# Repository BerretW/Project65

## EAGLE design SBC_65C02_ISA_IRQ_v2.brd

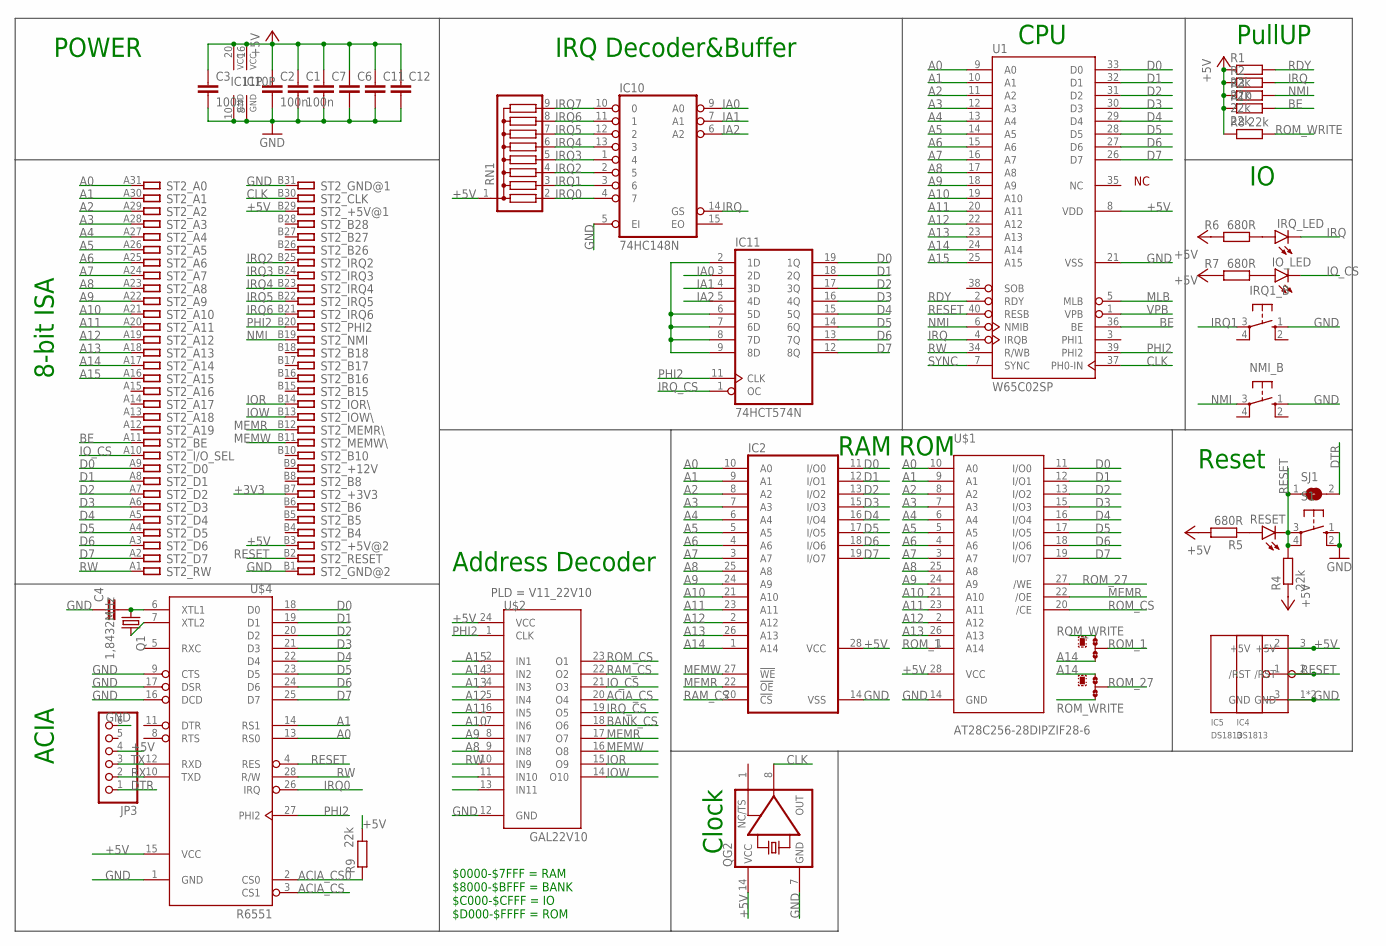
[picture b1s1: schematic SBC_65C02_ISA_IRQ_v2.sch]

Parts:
C1, C2, C3: 100n; C050-025X075
C4: C-EU025-030X050; C025-030X050
C6, C7, C11, C12: C-EU050-035X075; C050-035X075
IC2: 62256P; DIL28-6
IC4: DS1813; SOT223
IC5: DS1813; TO-92
IC10: 74HC148N; DIL16
IC11: 74HCT574N; DIL20
IO_LED: LED5MM
IRQ1_B: 10-XX; B3F-10XX
IRQ_LED: LED5MM
JP3: PINHD-1X6/90; 1X06/90
NMI_B: 10-XX; B3F-10XX
Q1: 1,8432MHz; HC49/S
QG2: XO-14; DIL14S
R1, R2, R3, R4, R8, R9, R10: 22k; 0207/10
R5, R6, R7: 680R; 0207/10
RESET: LED5MM
RN1: G08R; SIL9
ROM_1, ROM_27: 0R-JUMPA; A0R-JMP
S1: 10-XX; B3F-10XX
SJ1: SJ
ST2: IBM8BIT_ISA; IBM8BIT
U1: W65C02SP; DIP-40
U$1: AT28C256-28DIPZIF28-6; 228-1277-00-0602J
U$2: GAL22V10; DIL28_1
U$4: R6551; DIP-28

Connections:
+3V3: ST2.B7
+5V: C1.1, C2.1, C3.1, C6.1, C7.1, C11.1, C12.1, IC2.28 (VCC), IC4.3 (+5V), IC5.2 (+5V), IC10.16 (VCC), IC11.20 (VCC), JP3.4, QG2.14 (VCC), R1.1, R2.1, R3.1, R4.1, R5.2, R6.2, R7.2, R8.1, R9.2, R10.1, RN1.1, ST2.B3, ST2.B29, U1.8 (VDD), U$1.28 (VCC), U$2.24 (VCC), U$4.15 (VCC)
A0: IC2.10 (A0), ST2.A31, U1.9 (A0), U$1.10 (A0), U$4.13 (RS0)
A1: IC2.9 (A1), ST2.A30, U1.10 (A1), U$1.9 (A1), U$4.14 (RS1)
A2: IC2.8 (A2), ST2.A29, U1.11 (A2), U$1.8 (A2)
A3: IC2.7 (A3), ST2.A28, U1.12 (A3), U$1.7 (A3)
A4: IC2.6 (A4), ST2.A27, U1.13 (A4), U$1.6 (A4)
A5: IC2.5 (A5), ST2.A26, U1.14 (A5), U$1.5 (A5)
A6: IC2.4 (A6), ST2.A25, U1.15 (A6), U$1.4 (A6)
A7: IC2.3 (A7), ST2.A24, U1.16 (A7), U$1.3 (A7)
A8: IC2.25 (A8), ST2.A23, U1.17 (A8), U$1.25 (A8), U$2.9 (IN8)
A9: IC2.24 (A9), ST2.A22, U1.18 (A9), U$1.24 (A9), U$2.8 (IN7)
A10: IC2.21 (A10), ST2.A21, U1.19 (A10), U$1.21 (A10), U$2.7 (IN6)
A11: IC2.23 (A11), ST2.A20, U1.20 (A11), U$1.23 (A11), U$2.6 (IN5)
A12: IC2.2 (A12), ST2.A19, U1.22 (A12), U$1.2 (A12), U$2.5 (IN4)
A13: IC2.26 (A13), ST2.A18, U1.23 (A13), U$1.26 (A13), U$2.4 (IN3)
A14: IC2.1 (A14), ROM_1.3, ROM_27.1, ST2.A17, U1.24 (A14), U$2.3 (IN2)
A15: ST2.A16, U1.25 (A15), U$2.2 (IN1)
ACIA_CS: U$2.20 (O4), U$4.3 (CS1)
ACIA_CS0: R9.1, U$4.2 (CS0)
BANK_CS: U$2.18 (O6)
BE: R10.2, ST2.A11, U1.36 (BE)
CLK: QG2.8 (OUT), ST2.B30, U1.37 (PH0-IN)
D0: IC2.11 (I/O0), IC11.19 (1Q), ST2.A9, U1.33 (D0), U$1.11 (I/O0), U$4.18 (D0)
D1: IC2.12 (I/O1), IC11.18 (2Q), ST2.A8, U1.32 (D1), U$1.12 (I/O1), U$4.19 (D1)
D2: IC2.13 (I/O2), IC11.17 (3Q), ST2.A7, U1.31 (D2), U$1.13 (I/O2), U$4.20 (D2)
D3: IC2.15 (I/O3), IC11.16 (4Q), ST2.A6, U1.30 (D3), U$1.15 (I/O3), U$4.21 (D3)
D4: IC2.16 (I/O4), IC11.15 (5Q), ST2.A5, U1.29 (D4), U$1.16 (I/O4), U$4.22 (D4)
D5: IC2.17 (I/O5), IC11.14 (6Q), ST2.A4, U1.28 (D5), U$1.17 (I/O5), U$4.23 (D5)
D6: IC2.18 (I/O6), IC11.13 (7Q), ST2.A3, U1.27 (D6), U$1.18 (I/O6), U$4.24 (D6)
D7: IC2.19 (I/O7), IC11.12 (8Q), ST2.A2, U1.26 (D7), U$1.19 (I/O7), U$4.25 (D7)
DTR: JP3.1, SJ1.2
GND: C1.2, C2.2, C3.2, C4.1, C6.2, C7.2, C11.2, C12.2, IC2.14 (VSS), IC4.1 (GND), IC4.4 (GND), IC5.3 (GND), IC10.5 (EI), IC10.8 (GND), IC11.10 (GND), IRQ1_B.1 (S), JP3.6, NMI_B.1 (S), QG2.7 (GND), S1.1 (S), S1.2 (S1), ST2.B1, ST2.B31, U1.21 (VSS), U$1.14 (GND), U$2.12 (GND), U$4.1 (GND), U$4.9 (CTS), U$4.16 (DCD), U$4.17 (DSR)
IA0: IC10.9 (A0), IC11.3 (2D)
IA1: IC10.7 (A1), IC11.4 (3D)
IA2: IC10.6 (A2), IC11.5 (4D)
IOR: ST2.B14, U$2.15 (O9)
IOW: ST2.B13, U$2.14 (O10)
IO_CS: IO_LED.K (C), ST2.A10, U$2.21 (O3)
IRQ: IC10.14 (GS), IRQ_LED.K (C), R2.2, U1.4 (IRQB)
IRQ0: IC10.4 (7), RN1.2, U$4.26 (IRQ)
IRQ1: IC10.3 (6), IRQ1_B.3, RN1.3
IRQ2: IC10.2 (5), RN1.4, ST2.B25
IRQ3: IC10.1 (4), RN1.5, ST2.B24
IRQ4: IC10.13 (3), RN1.6, ST2.B23
IRQ5: IC10.12 (2), RN1.7, ST2.B22
IRQ6: IC10.11 (1), RN1.8, ST2.B21
IRQ7: IC10.10 (0), RN1.9
IRQ_CS: IC11.1 (OC), U$2.19 (O5)
MEMR: IC2.22 (!OE), ST2.B12, U$1.22 (/OE), U$2.17 (O7)
MEMW: IC2.27 (!WE), ST2.B11, U$2.16 (O8)
MLB: U1.5 (MLB)
unnamed: IRQ_LED.A, R6.1
unnamed: R5.1, RESET.A
unnamed: IO_LED.A, R7.1
unnamed: IC11.2 (1D), IC11.6 (5D), IC11.7 (6D), IC11.8 (7D), IC11.9 (8D)
unnamed: C4.2, Q1.1, U$4.6 (XTL1)
unnamed: Q1.2, U$4.7 (XTL2)
NMI: NMI_B.3, R3.2, ST2.B19, U1.6 (NMIB)
PHI2: IC11.11 (CLK), ST2.B20, U1.39 (PHI2), U$2.1 (CLK), U$4.27 (PHI2)
RAM_CS: IC2.20 (!CS), U$2.22 (O2)
RDY: R1.2, U1.2 (RDY)
RESET: IC4.2 (/RST), IC5.1 (/RST), R4.2, RESET.K (C), S1.3, S1.4 (P1), SJ1.1, ST2.B2, U1.40 (RESB), U$4.4 (RES)
ROM_1: ROM_1.2, U$1.1 (A14)
ROM_27: ROM_27.2, U$1.27 (/WE)
ROM_CS: U$1.20 (/CE), U$2.23 (O1)
ROM_WRITE: R8.2, ROM_1.1, ROM_27.3
RW: ST2.A1, U1.34 (R/WB), U$2.10 (IN9), U$4.28 (R/W)
RX: JP3.2, U$4.10 (TXD)
SYNC: U1.7 (SYNC)
TX: JP3.3, U$4.12 (RXD)
VPB: U1.1 (VPB)

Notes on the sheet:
$0000-$7FFF = RAM $8000-$BFFF = BANK $C000-$CFFF = IO $D000-$FFFF = ROM
ACIA
Address Decoder
Reset
CPU
POWER
8-bit ISA
RAM ROM
Clock
PullUP
PLD = V11_22V10
IRQ Decoder&Buffer

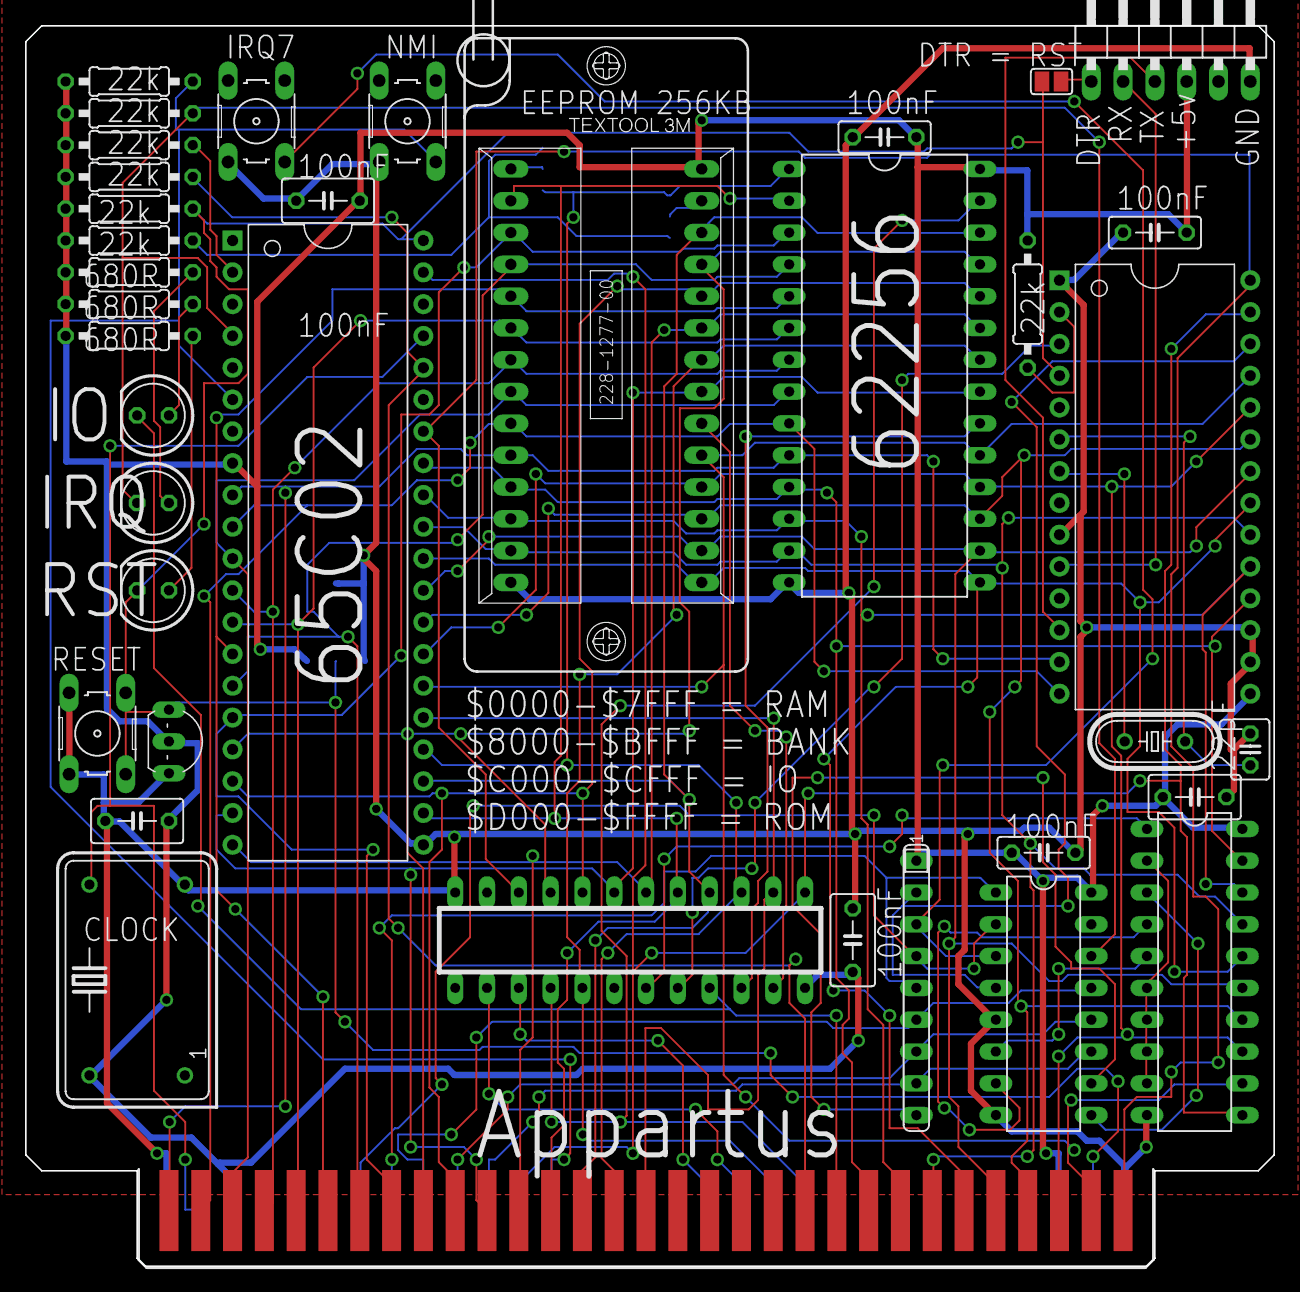
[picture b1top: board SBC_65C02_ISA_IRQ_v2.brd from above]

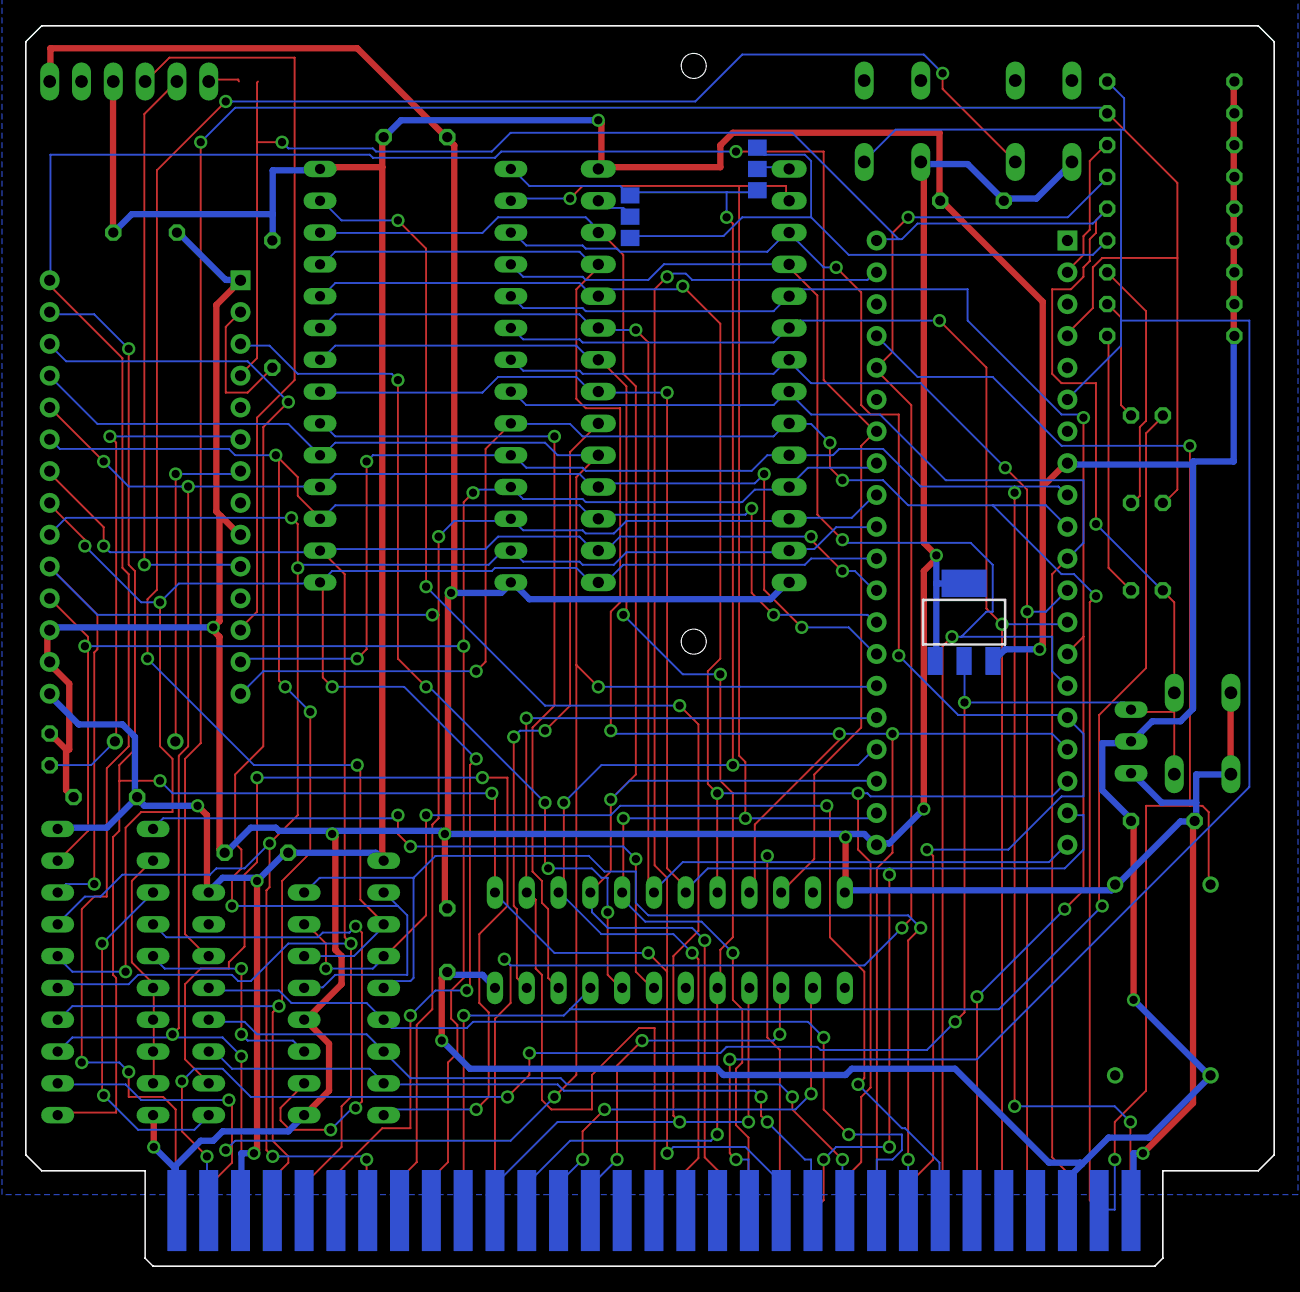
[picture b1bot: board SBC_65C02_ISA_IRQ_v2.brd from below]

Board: 2 copper layers, 99.7 x 99.1 mm, 41 parts (3 on the bottom side), 67 nets.

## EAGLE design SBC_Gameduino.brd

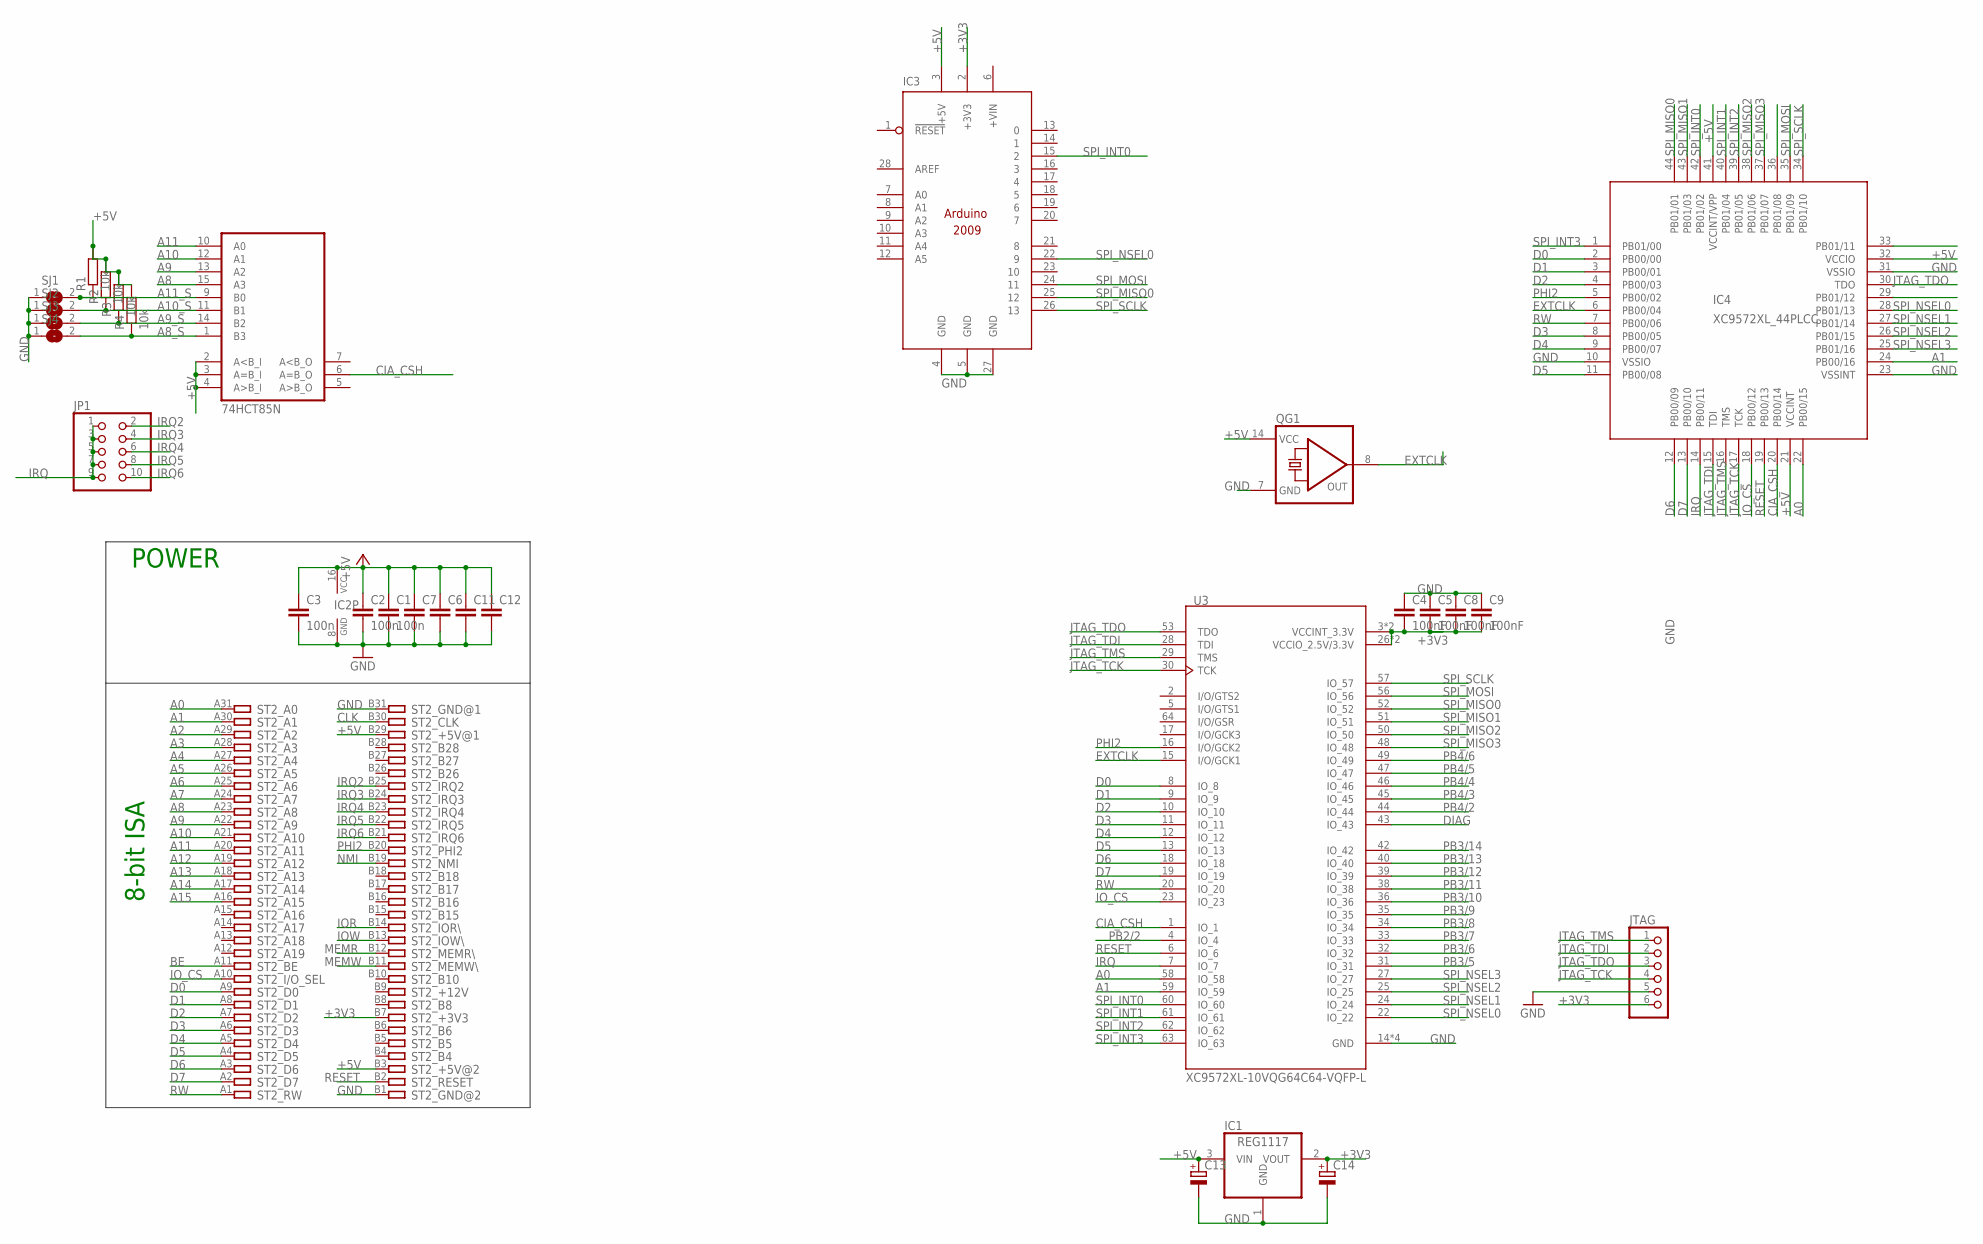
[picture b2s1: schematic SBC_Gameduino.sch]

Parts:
C1, C2, C3: 100n; C050-025X075
C4, C5, C8, C9: 100nF; C603
C6, C7, C11, C12: C-EU050-035X075; C050-035X075
C13, C14: CPOL-EUE2.5-5; E2,5-5
IC1: REG1117; SOT223
IC2: 74HCT85N; DIL16
IC3: ARDUINO2009_10; ARDUINO2009
IC4: XC9572XL_44PLCC; S44
JP1: PINHD-2X5; 2X05
JTAG: PINHD-1X6; 1X06
QG1: QG5860; DIL14S
R1, R2, R3, R4: 10k; 0207/7
SJ1, SJ2, SJ3, SJ4: SJ
ST2: IBM8BIT_ISASHORT; APP_2X32_SHORT
U3: XC9572XL-10VQG64C64-VQFP-L; VQFP64

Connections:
+3V3: C4.2, C5.2, C8.2, C9.2, C14.+, IC1.2 (VOUT), IC3.2 (+3V3), JTAG.6, ST2.B7, U3.3 (VCCINT_3.3V), U3.26 (VCCIO_2.5V/3.3V), U3.37 (VCCINT_3.3V), U3.55 (VCCIO_2.5V/3.3V)
+5V: C1.1, C2.1, C3.1, C6.1, C7.1, C11.1, C12.1, C13.+, IC1.3 (VIN), IC2.2 (A<B_I), IC2.3 (A=B_I), IC2.4 (A>B_I), IC2.16 (VCC), IC3.3 (+5V), IC4.21 (VCCINT), IC4.32 (VCCIO), IC4.41 (VCCINT/VPP), QG1.14 (VCC), R1.2, R2.2, R3.2, R4.2, ST2.B3, ST2.B29
A0: IC4.22 (PB00/15), ST2.A31, U3.58 (IO_58)
A1: IC4.24 (PB00/16), ST2.A30, U3.59 (IO_59)
A2: ST2.A29
A3: ST2.A28
A4: ST2.A27
A5: ST2.A26
A6: ST2.A25
A7: ST2.A24
A8: IC2.15 (A3), ST2.A23
A8_S: IC2.1 (B3), R4.1, SJ4.2
A9: IC2.13 (A2), ST2.A22
A9_S: IC2.14 (B2), R3.1, SJ3.2
A10: IC2.12 (A1), ST2.A21
A10_S: IC2.11 (B1), R2.1, SJ2.2
A11: IC2.10 (A0), ST2.A20
A11_S: IC2.9 (B0), R1.1, SJ1.2
A12: ST2.A19
A13: ST2.A18
A14: ST2.A17
A15: ST2.A16
BE: ST2.A11
CIA_CSH: IC2.6 (A=B_O), IC4.20 (PB00/14), U3.1 (IO_1)
CLK: ST2.B30
D0: IC4.2 (PB00/00), ST2.A9, U3.8 (IO_8)
D1: IC4.3 (PB00/01), ST2.A8, U3.9 (IO_9)
D2: IC4.4 (PB00/03), ST2.A7, U3.10 (IO_10)
D3: IC4.8 (PB00/05), ST2.A6, U3.11 (IO_11)
D4: IC4.9 (PB00/07), ST2.A5, U3.12 (IO_12)
D5: IC4.11 (PB00/08), ST2.A4, U3.13 (IO_13)
D6: IC4.12 (PB00/09), ST2.A3, U3.18 (IO_18)
D7: IC4.13 (PB00/10), ST2.A2, U3.19 (IO_19)
DIAG: U3.43 (IO_43)
EXTCLK: IC4.6 (PB00/04), QG1.8 (OUT), U3.15 (I/O/GCK1)
GND: C1.2, C2.2, C3.2, C4.1, C5.1, C6.2, C7.2, C8.1, C9.1, C11.2, C12.2, C13.-, C14.-, IC1.1 (GND), IC2.8 (GND), IC3.4 (GND), IC3.5 (GND), IC3.27 (GND), IC4.10 (VSSIO), IC4.23 (VSSINT), IC4.31 (VSSIO), JTAG.5, QG1.7 (GND), SJ1.1, SJ2.1, SJ3.1, SJ4.1, ST2.B1, ST2.B31, U3.14 (GND), U3.21 (GND), U3.41 (GND), U3.54 (GND)
IOR: ST2.B14
IOW: ST2.B13
IO_CS: IC4.18 (PB00/12), ST2.A10, U3.23 (IO_23)
IRQ: IC4.14 (PB00/11), JP1.1, JP1.3, JP1.5, JP1.7, JP1.9, U3.7 (IO_7)
IRQ2: JP1.2, ST2.B25
IRQ3: JP1.4, ST2.B24
IRQ4: JP1.6, ST2.B23
IRQ5: JP1.8, ST2.B22
IRQ6: JP1.10, ST2.B21
JTAG_TCK: IC4.17 (TCK), JTAG.4, U3.30 (TCK)
JTAG_TDI: IC4.15 (TDI), JTAG.2, U3.28 (TDI)
JTAG_TDO: IC4.30 (TDO), JTAG.3, U3.53 (TDO)
JTAG_TMS: IC4.16 (TMS), JTAG.1, U3.29 (TMS)
MEMR: ST2.B12
MEMW: ST2.B11
NMI: ST2.B19
PB2/2: U3.4 (IO_4)
PB3/5: U3.31 (IO_31)
PB3/6: U3.32 (IO_32)
PB3/7: U3.33 (IO_33)
PB3/8: U3.34 (IO_34)
PB3/9: U3.35 (IO_35)
PB3/10: U3.36 (IO_36)
PB3/11: U3.38 (IO_38)
PB3/12: U3.39 (IO_39)
PB3/13: U3.40 (IO_40)
PB3/14: U3.42 (IO_42)
PB4/2: U3.44 (IO_44)
PB4/3: U3.45 (IO_45)
PB4/4: U3.46 (IO_46)
PB4/5: U3.47 (IO_47)
PB4/6: U3.49 (IO_49)
PHI2: IC4.5 (PB00/02), ST2.B20, U3.16 (I/O/GCK2)
RESET: IC4.19 (PB00/13), ST2.B2, U3.6 (IO_6)
RW: IC4.7 (PB00/06), ST2.A1, U3.20 (IO_20)
SPI_INT0: IC3.15 (2), IC4.42 (PB01/02), U3.60 (IO_60)
SPI_INT1: IC4.40 (PB01/04), U3.61 (IO_61)
SPI_INT2: IC4.39 (PB01/05), U3.62 (IO_62)
SPI_INT3: IC4.1 (PB01/00), U3.63 (IO_63)
SPI_MISO0: IC3.25 (12), IC4.44 (PB01/01), U3.52 (IO_52)
SPI_MISO1: IC4.43 (PB01/03), U3.51 (IO_51)
SPI_MISO2: IC4.38 (PB01/06), U3.50 (IO_50)
SPI_MISO3: IC4.37 (PB01/07), U3.48 (IO_48)
SPI_MOSI: IC3.24 (11), IC4.35 (PB01/09), U3.56 (IO_56)
SPI_NSEL0: IC3.22 (9), IC4.28 (PB01/13), U3.22 (IO_22)
SPI_NSEL1: IC4.27 (PB01/14), U3.24 (IO_24)
SPI_NSEL2: IC4.26 (PB01/15), U3.25 (IO_25)
SPI_NSEL3: IC4.25 (PB01/16), U3.27 (IO_27)
SPI_SCLK: IC3.26 (13), IC4.34 (PB01/10), U3.57 (IO_57)

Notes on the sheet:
POWER
8-bit ISA

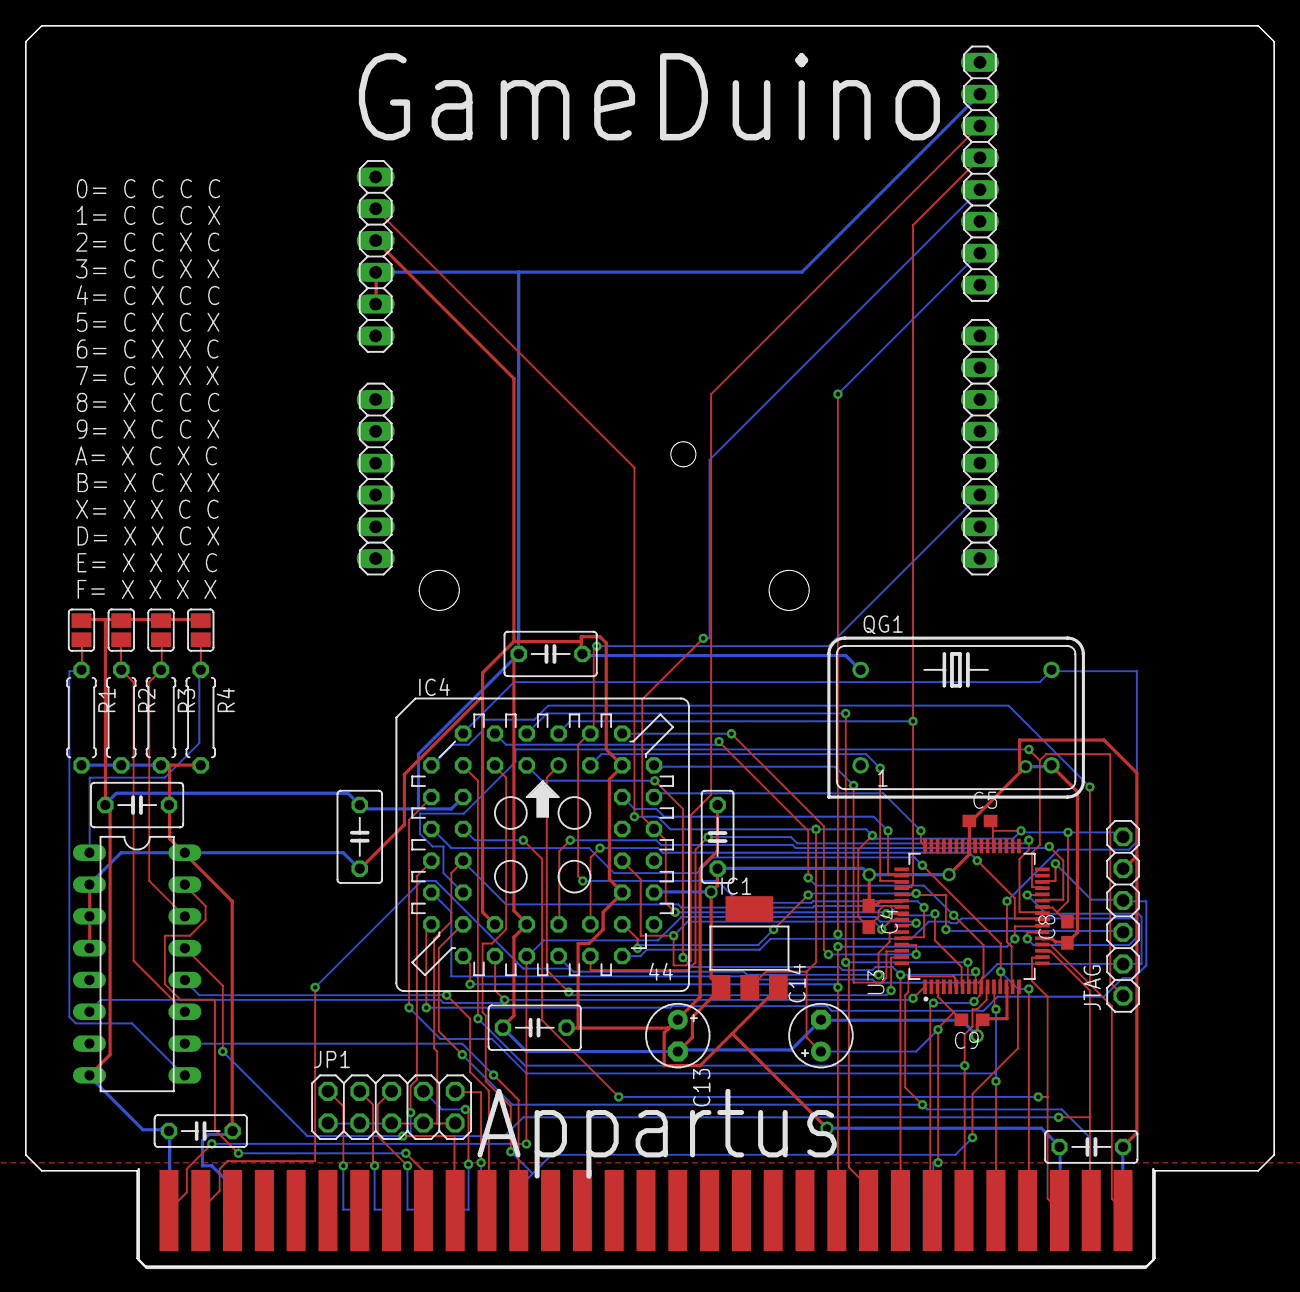
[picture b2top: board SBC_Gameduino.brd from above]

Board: 2 copper layers, 99.7 x 99.1 mm, 30 parts (0 on the bottom side), 51 nets.
